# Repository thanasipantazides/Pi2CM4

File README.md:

# Pi2CM4
An adapter board for the [Raspberry Pi Compute Module 4](https://datasheets.raspberrypi.com/cm4/cm4-datasheet.pdf) that has the footprint and I/O connectors of a Raspberry Pi 2/3/[4](https://datasheets.raspberrypi.com/rpi4/raspberry-pi-4-product-brief.pdf).

## WARNING: HAS NOT BEEN TESTED.
I will update when testing is done.

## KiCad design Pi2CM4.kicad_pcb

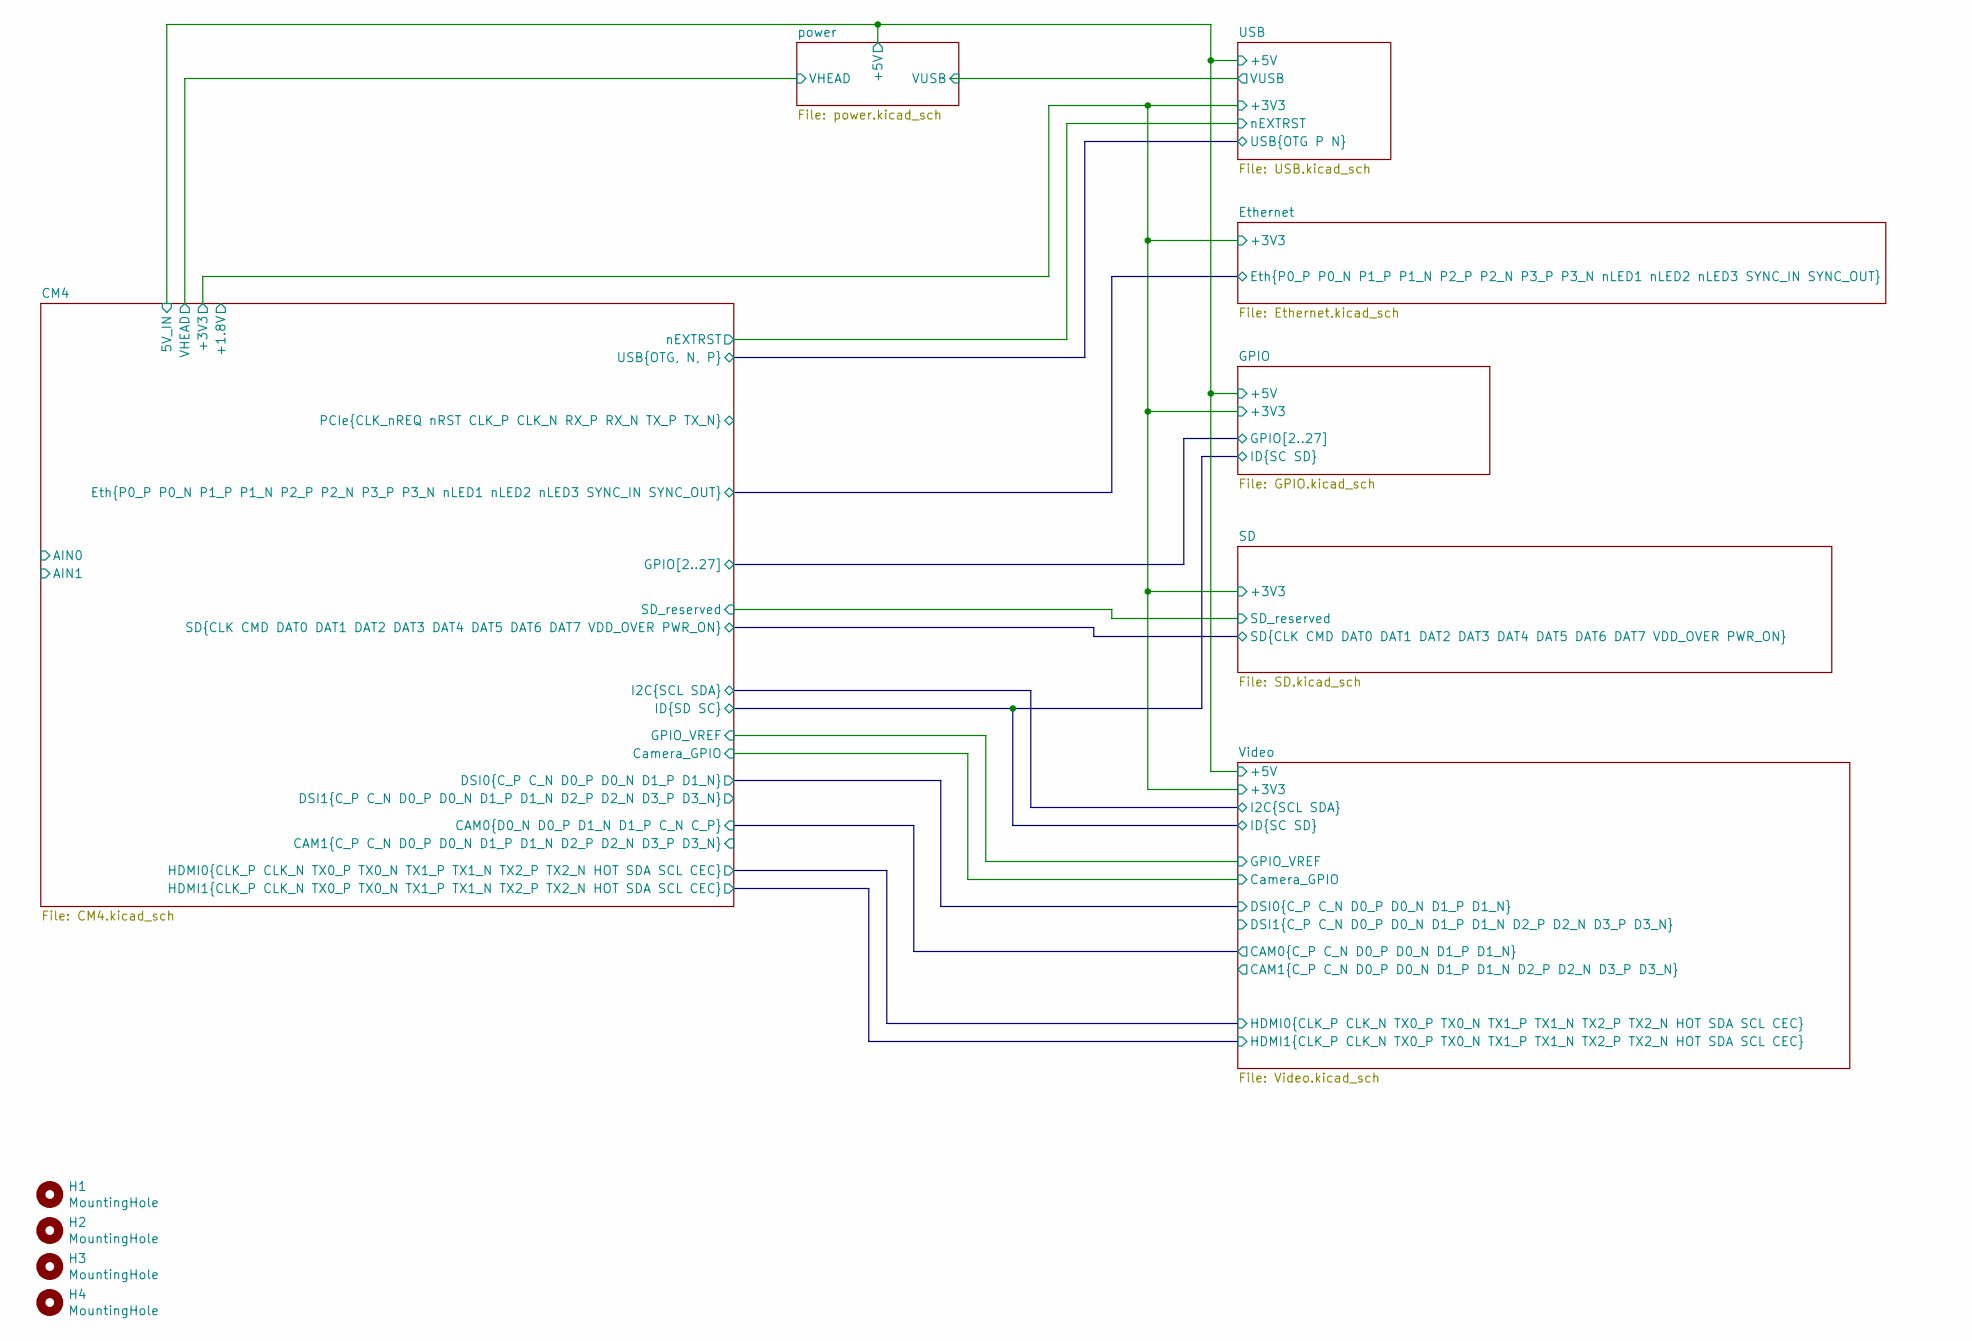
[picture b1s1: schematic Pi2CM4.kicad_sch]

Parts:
H1, H2, H3, H4: MountingHole; MountingHole_2.7mm_M2.5; Part Description M2.5 mounting hole

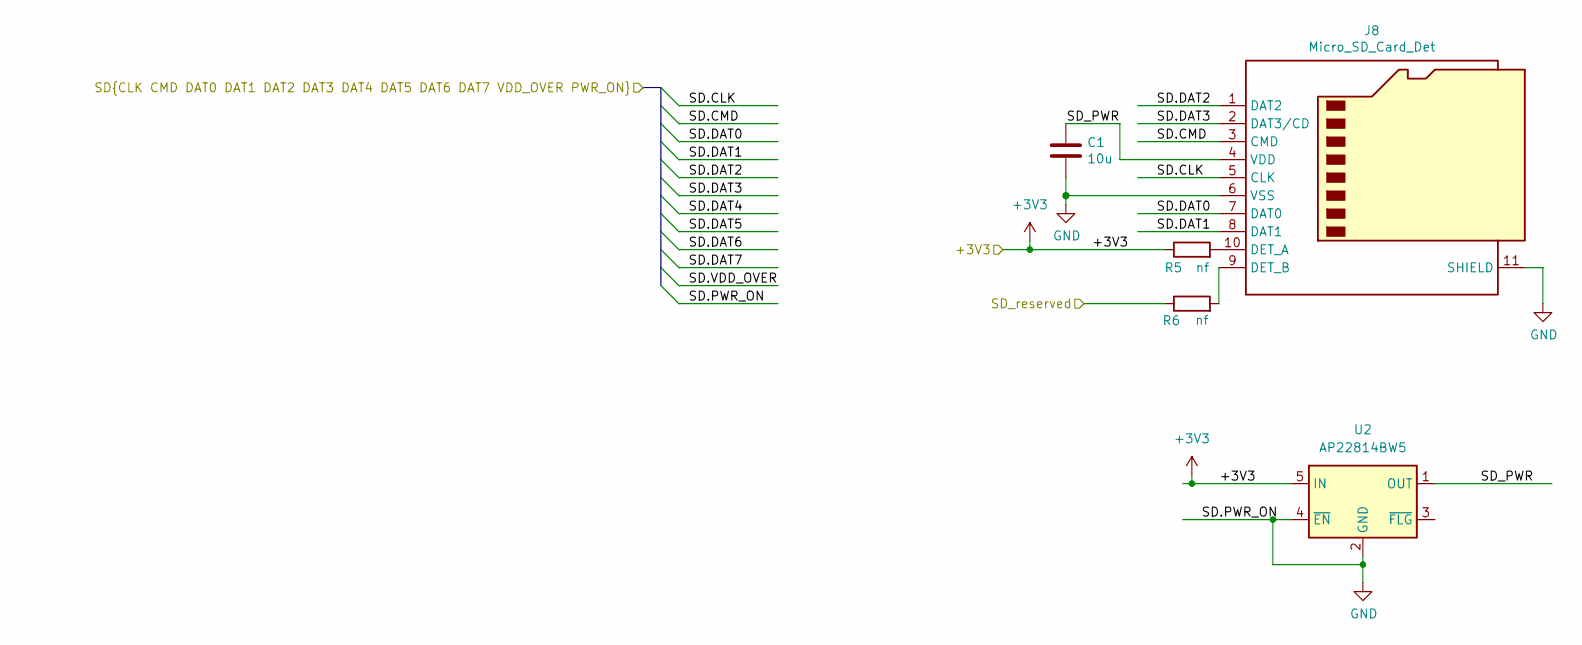
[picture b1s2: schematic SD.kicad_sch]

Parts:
C1: 10u; C_0805_2012Metric; Part Description 10uF 10% 10V Ceramic Capacitor X7R 0805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
J8: Micro_SD_Card_Det; SDCARD_MOLEX_503398-1892; Part Description 9 (8 + 1) Position Card Connector micro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
R5, R6: nf; R_0402_1005Metric; Part Description Resistor 1K M1005 1% 63mW
U2: AP22814BW5; SOT-23-5

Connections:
+3V3: R5.1, U2.5 (IN); also elsewhere on the board
/CM4/SD.CLK: J8.5 (CLK); also elsewhere on the board
/CM4/SD.CMD: J8.3 (CMD); also elsewhere on the board
/CM4/SD.DAT0: J8.7 (DAT0); also elsewhere on the board
/CM4/SD.DAT1: J8.8 (DAT1); also elsewhere on the board
/CM4/SD.DAT2: J8.1 (DAT2); also elsewhere on the board
/CM4/SD.DAT3: J8.2 (DAT3/CD); also elsewhere on the board
/CM4/SD_reserved: R6.1; also elsewhere on the board
/SD/SD_PWR: C1.1, J8.4 (VDD), U2.1 (OUT)
GND: C1.2, J8.6 (VSS), J8.11 (SHIELD), U2.2 (GND), U2.4 (~EN); also elsewhere on the board
unnamed: J8.9 (DET_B), R6.2
unnamed: J8.10 (DET_A), R5.2

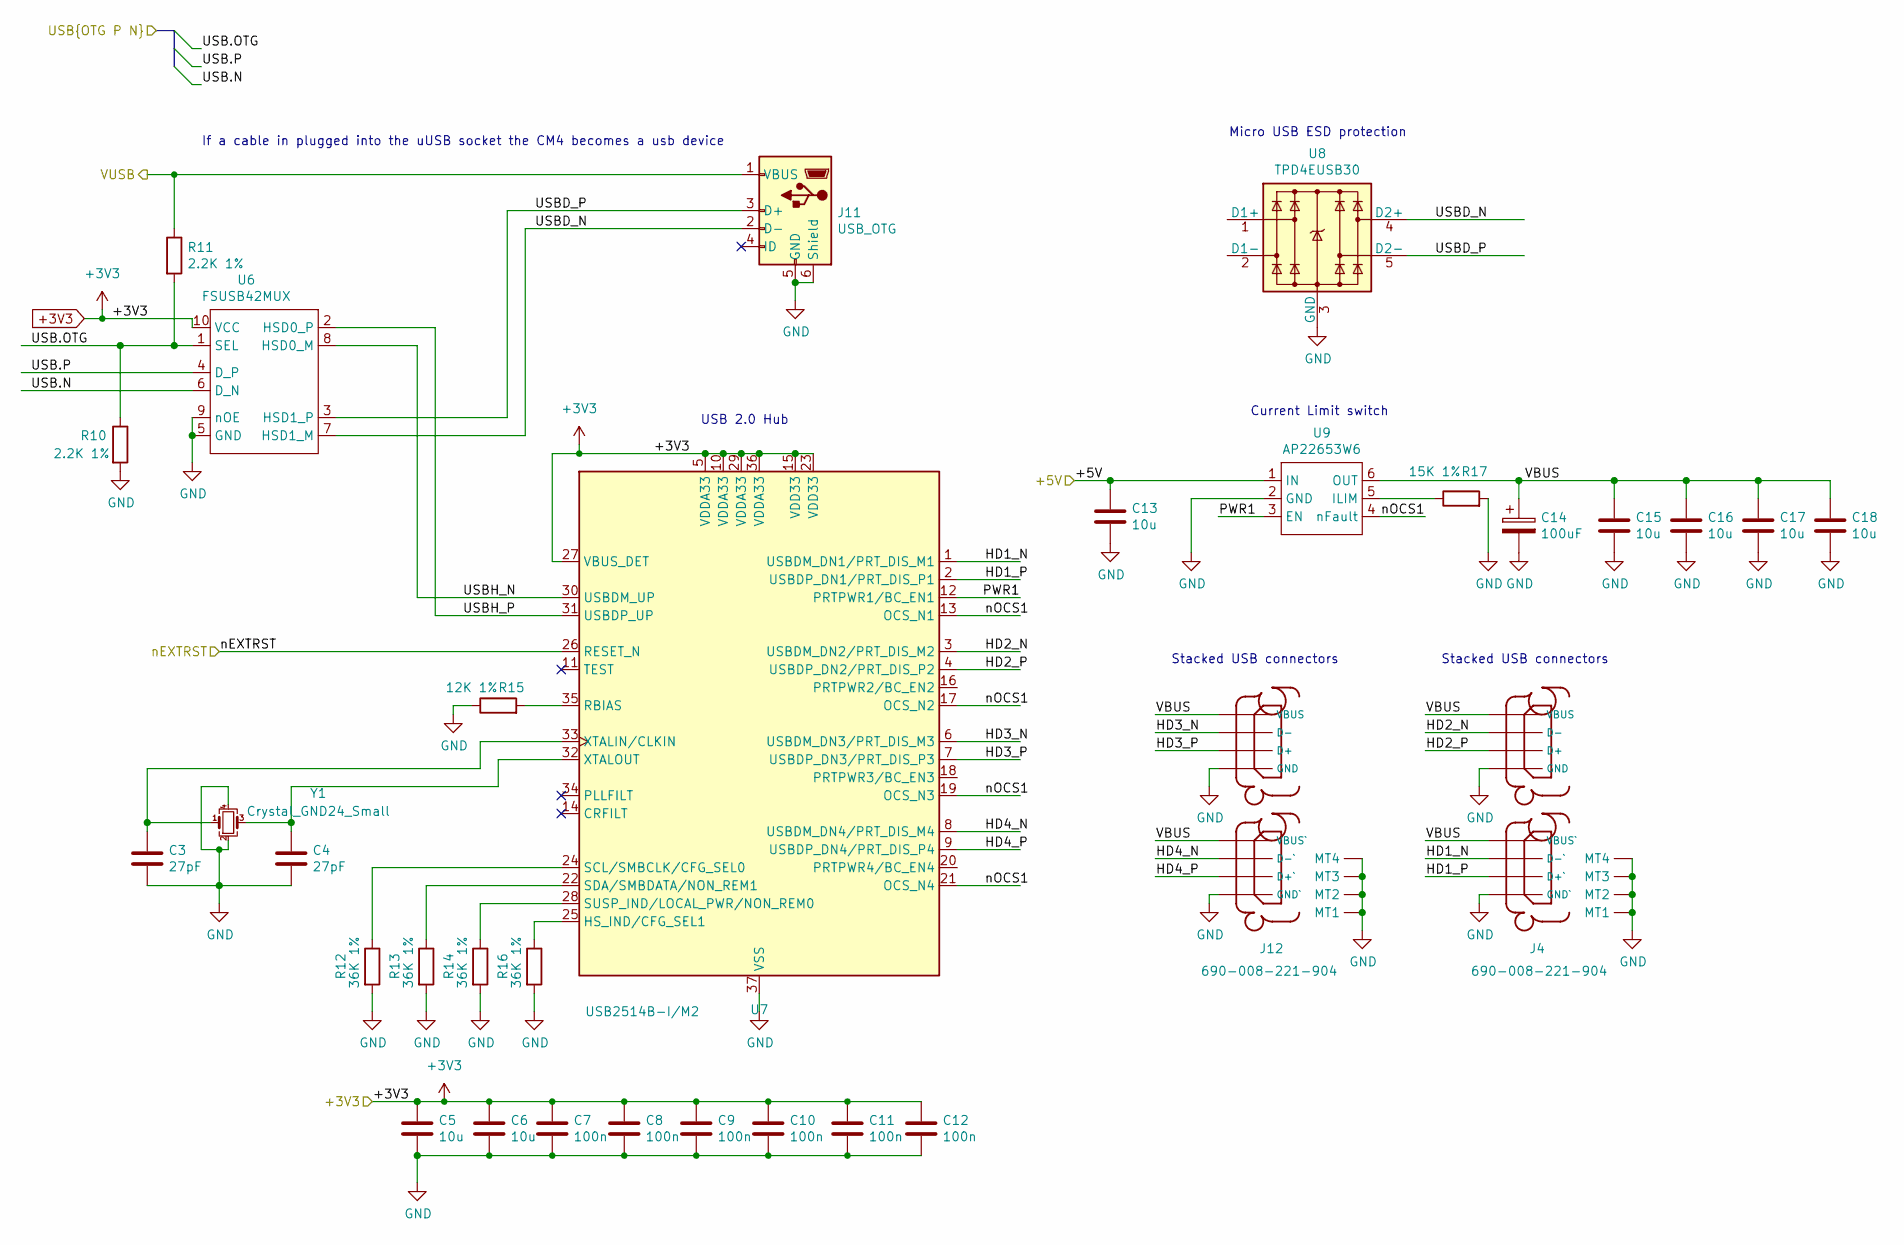
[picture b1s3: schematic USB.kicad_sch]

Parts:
C3, C4: 27pF; C_0402_1005Metric; Part Description 27pF 5% 50V Ceramic Capacitor C0G, NP0 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
C5, C6, C13, C15, C16, C17, C18: 10u; C_0805_2012Metric; Part Description 10uF 10% 10V Ceramic Capacitor X7R 0805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
C7, C8, C9, C10, C11, C12: 100n; C_0402_1005Metric; Part Description 0.1uF 10% 16V Ceramic Capacitor X7R 040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
C14: 100uF; C_1210_3225Metric; Part Description Capacitor, SP-Cap, 100u, 6.3V, 15mR ESR
J4, J12: 690-008-221-904; MOLEX_USB_67298-4090; Part Description USB-A (USB TYPE-A), Stacked Receptacle 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
J11: USB_OTG; USB_Micro-B_EDAC_UCON00686; Part Description USB - micro B USB 2.0 Receptacle Connec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
R10, R11: 2.2K 1%; R_0402_1005Metric; Part Description Resistor 2.2K M1005 1% 63mW
R12, R13, R14, R16: 36K 1%; R_0402_1005Metric; Part Description Resistor 36K M1005 1% 63mW
R15: 12K 1%; R_0402_1005Metric; Part Description Resistor 12K M1005 1% 63mW
R17: 15K 1%; R_0402_1005Metric; Part Description Resistor 15K M1005 1% 63mW
U6: FSUSB42MUX; Texas_R-PUQFN-N10; Part Description USB Switch IC 1 Channel 10-MSOP
U7: USB2514B-I/M2; QFN-36-1EP_6x6mm_P0.5mm_EP3.7x3.7mm; Part Description USB Hub Controller USB Interface 36-SQF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
U8: TPD4EUSB30; USON-10_2.5x1.0mm_P0.5mm; Part Description Quad TVS diode for high speed signals (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
U9: AP22653W6; SOT-23-6; Part Description Power Switch/Driver 1:1 P-Channel 2.1A 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
Y1: Crystal_GND24_Small; Crystal_SMD_2520-4Pin_2.5x2.0mm

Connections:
+3V3: C5.1, C6.1, C7.1, C8.1, C9.1, C10.1, C11.1, C12.1, U6.10 (VCC), U7.5 (VDDA33), U7.10 (VDDA33), U7.15 (VDD33), U7.23 (VDD33), U7.27 (VBUS_DET), U7.29 (VDDA33), U7.36 (VDDA33); also elsewhere on the board
+5V: C13.1, U9.1 (IN); also elsewhere on the board
/CM4/USB.N: U6.6 (D_N); also elsewhere on the board
/CM4/USB.OTG: R10.1, R11.2, U6.1 (SEL); also elsewhere on the board
/CM4/USB.P: U6.4 (D_P); also elsewhere on the board
/CM4/nEXTRST: U7.26 (RESET_N); also elsewhere on the board
/USB/HD1_N: J4.2 (D-`), U7.1 (USBDM_DN1/PRT_DIS_M1)
/USB/HD1_P: J4.3 (D+`), U7.2 (USBDP_DN1/PRT_DIS_P1)
/USB/HD2_N: J4.6 (D-), U7.3 (USBDM_DN2/PRT_DIS_M2)
/USB/HD2_P: J4.7 (D+), U7.4 (USBDP_DN2/PRT_DIS_P2)
/USB/HD3_N: J12.6 (D-), U7.6 (USBDM_DN3/PRT_DIS_M3)
/USB/HD3_P: J12.7 (D+), U7.7 (USBDP_DN3/PRT_DIS_P3)
/USB/HD4_N: J12.2 (D-`), U7.8 (USBDM_DN4/PRT_DIS_M4)
/USB/HD4_P: J12.3 (D+`), U7.9 (USBDP_DN4/PRT_DIS_P4)
/USB/PWR1: U7.12 (PRTPWR1/BC_EN1), U9.3 (EN)
/USB/USBD_N: J11.2 (D-), U6.7 (HSD1_M), U8.4 (D2+), U8.7
/USB/USBD_P: J11.3 (D+), U6.3 (HSD1_P), U8.5 (D2-), U8.6
/USB/USBH_N: U6.8 (HSD0_M), U7.30 (USBDM_UP)
/USB/USBH_P: U6.2 (HSD0_P), U7.31 (USBDP_UP)
/USB/VBUS: C14.1, C15.1, C16.1, C17.1, C18.1, J4.1 (VBUS`), J4.5 (VBUS), J12.1 (VBUS`), J12.5 (VBUS), U9.6 (OUT)
/USB/VUSB: J11.1 (VBUS), R11.1
/USB/nOCS1: U7.13 (OCS_N1), U7.17 (OCS_N2), U7.19 (OCS_N3), U7.21 (OCS_N4), U9.4 (nFault)
GND: C3.2, C4.2, C5.2, C6.2, C7.2, C8.2, C9.2, C10.2, C11.2, C12.2, C13.2, C14.2, C15.2, C16.2, C17.2, C18.2, J4.4 (GND`), J4.8 (GND), J4.MT1, J4.MT2, J4.MT3, J4.MT4, J11.5 (GND), J11.6 (Shield), J12.4 (GND`), J12.8 (GND), J12.MT1, J12.MT2, J12.MT3, J12.MT4, R10.2, R12.2, R13.2, R14.2, R15.1, R16.2, R17.2, U6.5 (GND), U6.9 (nOE), U7.37 (VSS), U8.3 (GND), U8.8 (GND), U9.2 (GND), Y1.2, Y1.4; also elsewhere on the board
unnamed: C3.1, U7.33 (XTALIN/CLKIN), Y1.1
unnamed: C4.1, U7.32 (XTALOUT), Y1.3
unnamed: R12.1, U7.24 (SCL/SMBCLK/CFG_SEL0)
unnamed: R13.1, U7.22 (SDA/SMBDATA/NON_REM1)
unnamed: R14.1, U7.28 (SUSP_IND/LOCAL_PWR/NON_REM0)
unnamed: R15.2, U7.35 (RBIAS)
unnamed: R16.1, U7.25 (HS_IND/CFG_SEL1)
unnamed: R17.1, U9.5 (ILIM)
unnamed: U8.1 (D1+), U8.10
unnamed: U8.2 (D1-), U8.9

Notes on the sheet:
Current Limit switch
Stacked USB connectors
Micro USB ESD protection
If a cable in plugged into the uUSB socket the CM4 becomes a usb device
USB 2.0 Hub

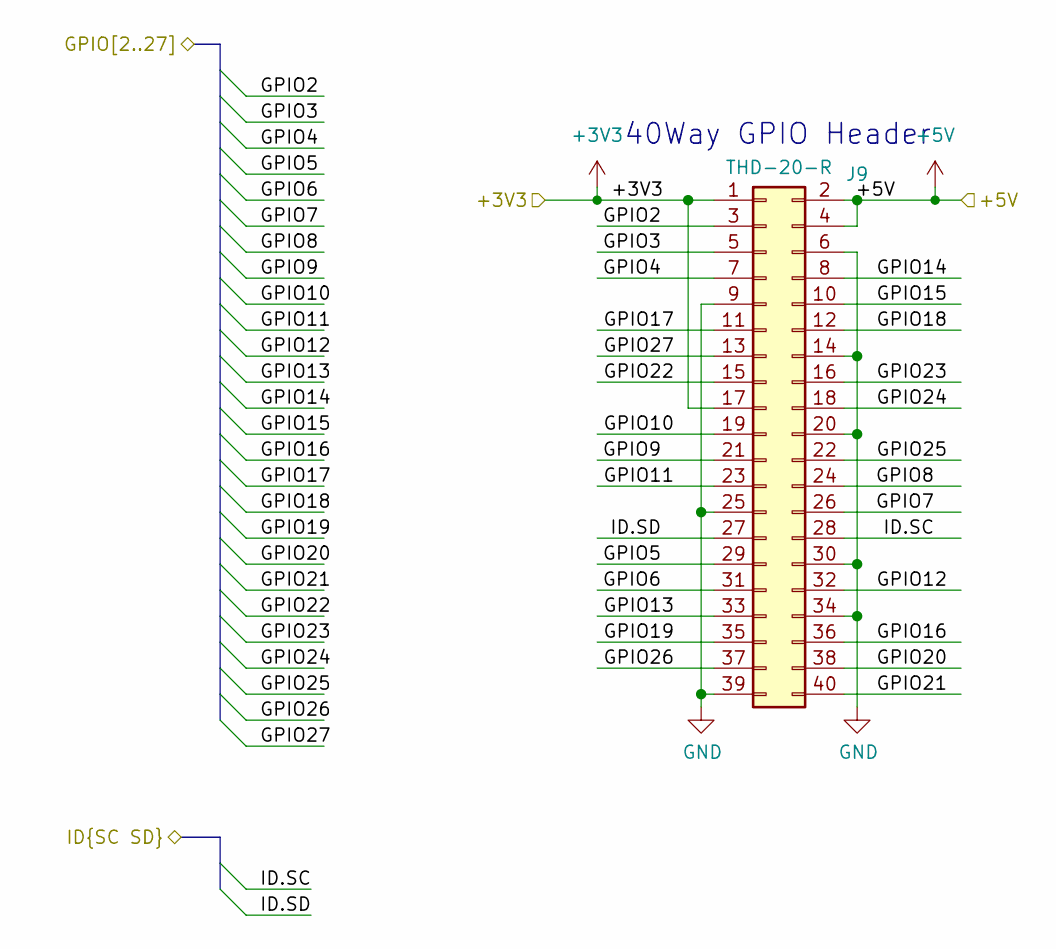
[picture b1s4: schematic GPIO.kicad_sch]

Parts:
J9: THD-20-R; PinHeader_2x20_P2.54mm_Vertical; Part Description PinHeader_2x20_P2.54mm_Vertical

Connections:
+3V3: J9.1, J9.17; also elsewhere on the board
+5V: J9.2, J9.4; also elsewhere on the board
/CM4/GPIO2: J9.3; also elsewhere on the board
/CM4/GPIO3: J9.5; also elsewhere on the board
/CM4/GPIO4: J9.7; also elsewhere on the board
/CM4/GPIO5: J9.29; also elsewhere on the board
/CM4/GPIO6: J9.31; also elsewhere on the board
/CM4/GPIO7: J9.26; also elsewhere on the board
/CM4/GPIO8: J9.24; also elsewhere on the board
/CM4/GPIO9: J9.21; also elsewhere on the board
/CM4/GPIO10: J9.19; also elsewhere on the board
/CM4/GPIO11: J9.23; also elsewhere on the board
/CM4/GPIO12: J9.32; also elsewhere on the board
/CM4/GPIO13: J9.33; also elsewhere on the board
/CM4/GPIO14: J9.8; also elsewhere on the board
/CM4/GPIO15: J9.10; also elsewhere on the board
/CM4/GPIO16: J9.36; also elsewhere on the board
/CM4/GPIO17: J9.11; also elsewhere on the board
/CM4/GPIO18: J9.12; also elsewhere on the board
/CM4/GPIO19: J9.35; also elsewhere on the board
/CM4/GPIO20: J9.38; also elsewhere on the board
/CM4/GPIO21: J9.40; also elsewhere on the board
/CM4/GPIO22: J9.15; also elsewhere on the board
/CM4/GPIO23: J9.16; also elsewhere on the board
/CM4/GPIO24: J9.18; also elsewhere on the board
/CM4/GPIO25: J9.22; also elsewhere on the board
/CM4/GPIO26: J9.37; also elsewhere on the board
/CM4/GPIO27: J9.13; also elsewhere on the board
/CM4/ID.SC: J9.28; also elsewhere on the board
/CM4/ID.SD: J9.27; also elsewhere on the board
GND: J9.6, J9.9, J9.14, J9.20, J9.25, J9.30, J9.34, J9.39; also elsewhere on the board

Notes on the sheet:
40Way GPIO Header

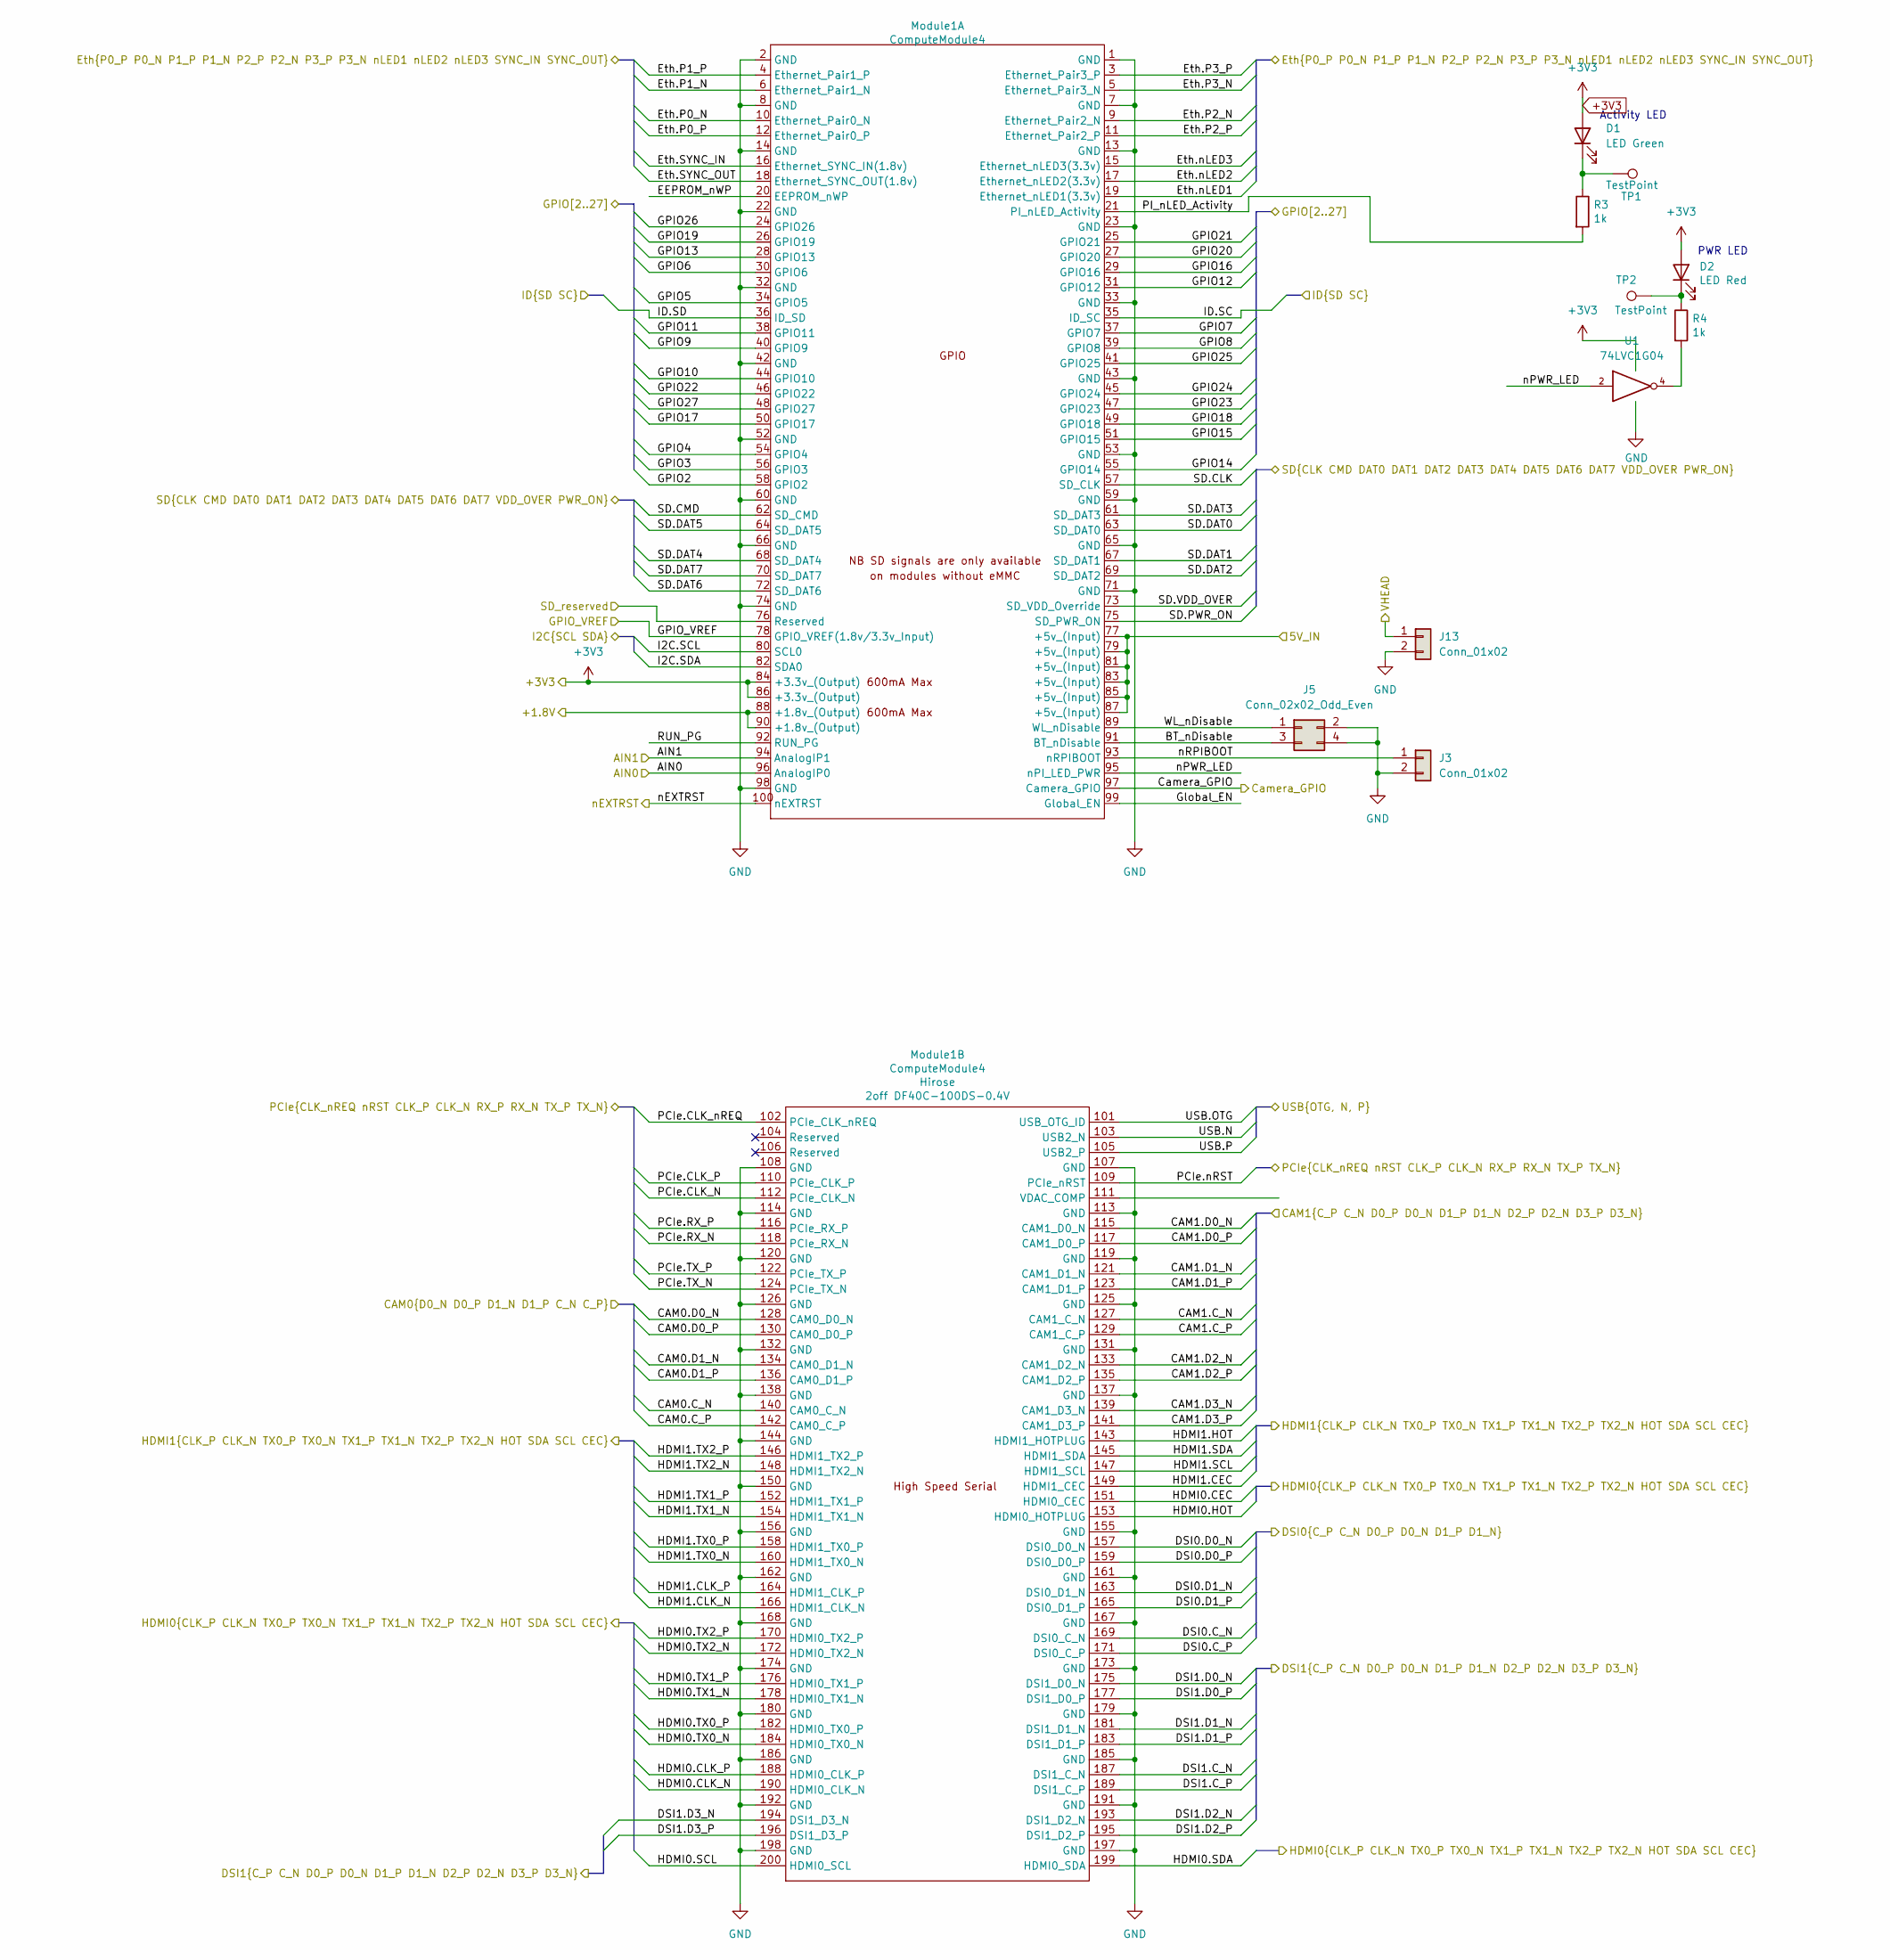
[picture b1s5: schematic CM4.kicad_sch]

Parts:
D1: LED Green; LED_0603_1608Metric; Part Description Green 572nm LED Indication - Discrete 2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
D2: LED Red; LED_0603_1608Metric; Part Description Red 620nm LED Indication - Discrete 2.2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
J3: Conn_01x02; PinHeader_1x02_P2.54mm_Vertical
J5: Conn_02x02_Odd_Even; PinSocket_2x02_P2.54mm_Vertical
J13: Conn_01x02; PinSocket_1x02_P2.54mm_Vertical
Module1: ComputeModule4; Raspberry-Pi-4-Compute-Module; Part Description 100 Position Connector Receptacle, Cent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
R3, R4: 1k; R_0402_1005Metric; Part Description Resistor 1K M1005 1% 63mW
TP1, TP2: TestPoint; TestPoint_Pad_2.0x2.0mm
U1: 74LVC1G04; SOT-23-5

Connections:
+3V3: D1.2 (A), D2.2 (A), Module1.84 (+3.3v_(Output)), Module1.86 (+3.3v_(Output)), U1.5 (VCC); also elsewhere on the board
+5V: Module1.77 (+5v_(Input)), Module1.79 (+5v_(Input)), Module1.81 (+5v_(Input)), Module1.83 (+5v_(Input)), Module1.85 (+5v_(Input)), Module1.87 (+5v_(Input)); also elsewhere on the board
/CM4/+1.8V: Module1.88 (+1.8v_(Output)), Module1.90 (+1.8v_(Output))
/CM4/AIN0: Module1.96 (AnalogIP0)
/CM4/AIN1: Module1.94 (AnalogIP1)
/CM4/BT_nDisable: J5.3, Module1.91 (BT_nDisable)
/CM4/CAM0.C_N: Module1.140 (CAM0_C_N); also elsewhere on the board
/CM4/CAM0.C_P: Module1.142 (CAM0_C_P); also elsewhere on the board
/CM4/CAM0.D0_N: Module1.128 (CAM0_D0_N); also elsewhere on the board
/CM4/CAM0.D0_P: Module1.130 (CAM0_D0_P); also elsewhere on the board
/CM4/CAM0.D1_N: Module1.134 (CAM0_D1_N); also elsewhere on the board
/CM4/CAM0.D1_P: Module1.136 (CAM0_D1_P); also elsewhere on the board
/CM4/CAM1.C_N: Module1.127 (CAM1_C_N)
/CM4/CAM1.C_P: Module1.129 (CAM1_C_P)
/CM4/CAM1.D0_N: Module1.115 (CAM1_D0_N)
/CM4/CAM1.D0_P: Module1.117 (CAM1_D0_P)
/CM4/CAM1.D1_N: Module1.121 (CAM1_D1_N)
/CM4/CAM1.D1_P: Module1.123 (CAM1_D1_P)
/CM4/CAM1.D2_N: Module1.133 (CAM1_D2_N)
/CM4/CAM1.D2_P: Module1.135 (CAM1_D2_P)
/CM4/CAM1.D3_N: Module1.139 (CAM1_D3_N)
/CM4/CAM1.D3_P: Module1.141 (CAM1_D3_P)
/CM4/Camera_GPIO: Module1.97 (Camera_GPIO); also elsewhere on the board
/CM4/DSI0.C_N: Module1.169 (DSI0_C_N); also elsewhere on the board
/CM4/DSI0.C_P: Module1.171 (DSI0_C_P); also elsewhere on the board
/CM4/DSI0.D0_N: Module1.157 (DSI0_D0_N); also elsewhere on the board
/CM4/DSI0.D0_P: Module1.159 (DSI0_D0_P); also elsewhere on the board
/CM4/DSI0.D1_N: Module1.163 (DSI0_D1_N); also elsewhere on the board
/CM4/DSI0.D1_P: Module1.165 (DSI0_D1_P); also elsewhere on the board
/CM4/DSI1.C_N: Module1.187 (DSI1_C_N)
/CM4/DSI1.C_P: Module1.189 (DSI1_C_P)
/CM4/DSI1.D0_N: Module1.175 (DSI1_D0_N)
/CM4/DSI1.D0_P: Module1.177 (DSI1_D0_P)
/CM4/DSI1.D1_N: Module1.181 (DSI1_D1_N)
/CM4/DSI1.D1_P: Module1.183 (DSI1_D1_P)
/CM4/DSI1.D2_N: Module1.193 (DSI1_D2_N)
/CM4/DSI1.D2_P: Module1.195 (DSI1_D2_P)
/CM4/DSI1.D3_N: Module1.194 (DSI1_D3_N)
/CM4/DSI1.D3_P: Module1.196 (DSI1_D3_P)
/CM4/EEPROM_nWP: Module1.20 (EEPROM_nWP)
/CM4/Eth.P0_N: Module1.10 (Ethernet_Pair0_N); also elsewhere on the board
/CM4/Eth.P0_P: Module1.12 (Ethernet_Pair0_P); also elsewhere on the board
/CM4/Eth.P1_N: Module1.6 (Ethernet_Pair1_N); also elsewhere on the board
/CM4/Eth.P1_P: Module1.4 (Ethernet_Pair1_P); also elsewhere on the board
/CM4/Eth.P2_N: Module1.9 (Ethernet_Pair2_N); also elsewhere on the board
/CM4/Eth.P2_P: Module1.11 (Ethernet_Pair2_P); also elsewhere on the board
/CM4/Eth.P3_N: Module1.5 (Ethernet_Pair3_N); also elsewhere on the board
/CM4/Eth.P3_P: Module1.3 (Ethernet_Pair3_P); also elsewhere on the board
/CM4/Eth.SYNC_IN: Module1.16 (Ethernet_SYNC_IN(1.8v))
/CM4/Eth.SYNC_OUT: Module1.18 (Ethernet_SYNC_OUT(1.8v))
/CM4/Eth.nLED1: Module1.19 (Ethernet_nLED1(3.3v))
/CM4/Eth.nLED2: Module1.17 (Ethernet_nLED2(3.3v)); also elsewhere on the board
/CM4/Eth.nLED3: Module1.15 (Ethernet_nLED3(3.3v)); also elsewhere on the board
/CM4/GPIO2: Module1.58 (GPIO2); also elsewhere on the board
/CM4/GPIO3: Module1.56 (GPIO3); also elsewhere on the board
/CM4/GPIO4: Module1.54 (GPIO4); also elsewhere on the board
/CM4/GPIO5: Module1.34 (GPIO5); also elsewhere on the board
/CM4/GPIO6: Module1.30 (GPIO6); also elsewhere on the board
/CM4/GPIO7: Module1.37 (GPIO7); also elsewhere on the board
/CM4/GPIO8: Module1.39 (GPIO8); also elsewhere on the board
/CM4/GPIO9: Module1.40 (GPIO9); also elsewhere on the board
/CM4/GPIO10: Module1.44 (GPIO10); also elsewhere on the board
/CM4/GPIO11: Module1.38 (GPIO11); also elsewhere on the board
/CM4/GPIO12: Module1.31 (GPIO12); also elsewhere on the board
/CM4/GPIO13: Module1.28 (GPIO13); also elsewhere on the board
/CM4/GPIO14: Module1.55 (GPIO14); also elsewhere on the board
/CM4/GPIO15: Module1.51 (GPIO15); also elsewhere on the board
/CM4/GPIO16: Module1.29 (GPIO16); also elsewhere on the board
/CM4/GPIO17: Module1.50 (GPIO17); also elsewhere on the board
/CM4/GPIO18: Module1.49 (GPIO18); also elsewhere on the board
/CM4/GPIO19: Module1.26 (GPIO19); also elsewhere on the board
/CM4/GPIO20: Module1.27 (GPIO20); also elsewhere on the board
/CM4/GPIO21: Module1.25 (GPIO21); also elsewhere on the board
/CM4/GPIO22: Module1.46 (GPIO22); also elsewhere on the board
/CM4/GPIO23: Module1.47 (GPIO23); also elsewhere on the board
/CM4/GPIO24: Module1.45 (GPIO24); also elsewhere on the board
/CM4/GPIO25: Module1.41 (GPIO25); also elsewhere on the board
/CM4/GPIO26: Module1.24 (GPIO26); also elsewhere on the board
/CM4/GPIO27: Module1.48 (GPIO27); also elsewhere on the board
/CM4/GPIO_VREF: Module1.78 (GPIO_VREF(1.8v/3.3v_Input)); also elsewhere on the board
/CM4/Global_EN: Module1.99 (Global_EN)
/CM4/HDMI0.CEC: Module1.151 (HDMI0_CEC); also elsewhere on the board
/CM4/HDMI0.CLK_N: Module1.190 (HDMI0_CLK_N); also elsewhere on the board
/CM4/HDMI0.CLK_P: Module1.188 (HDMI0_CLK_P); also elsewhere on the board
/CM4/HDMI0.HOT: Module1.153 (HDMI0_HOTPLUG); also elsewhere on the board
/CM4/HDMI0.SCL: Module1.200 (HDMI0_SCL); also elsewhere on the board
/CM4/HDMI0.SDA: Module1.199 (HDMI0_SDA); also elsewhere on the board
/CM4/HDMI0.TX0_N: Module1.184 (HDMI0_TX0_N); also elsewhere on the board
/CM4/HDMI0.TX0_P: Module1.182 (HDMI0_TX0_P); also elsewhere on the board
/CM4/HDMI0.TX1_N: Module1.178 (HDMI0_TX1_N); also elsewhere on the board
/CM4/HDMI0.TX1_P: Module1.176 (HDMI0_TX1_P); also elsewhere on the board
/CM4/HDMI0.TX2_N: Module1.172 (HDMI0_TX2_N); also elsewhere on the board
/CM4/HDMI0.TX2_P: Module1.170 (HDMI0_TX2_P); also elsewhere on the board
/CM4/HDMI1.CEC: Module1.149 (HDMI1_CEC); also elsewhere on the board
/CM4/HDMI1.CLK_N: Module1.166 (HDMI1_CLK_N); also elsewhere on the board
/CM4/HDMI1.CLK_P: Module1.164 (HDMI1_CLK_P); also elsewhere on the board
/CM4/HDMI1.HOT: Module1.143 (HDMI1_HOTPLUG); also elsewhere on the board
/CM4/HDMI1.SCL: Module1.147 (HDMI1_SCL); also elsewhere on the board
/CM4/HDMI1.SDA: Module1.145 (HDMI1_SDA); also elsewhere on the board
/CM4/HDMI1.TX0_N: Module1.160 (HDMI1_TX0_N); also elsewhere on the board
/CM4/HDMI1.TX0_P: Module1.158 (HDMI1_TX0_P); also elsewhere on the board
/CM4/HDMI1.TX1_N: Module1.154 (HDMI1_TX1_N); also elsewhere on the board
/CM4/HDMI1.TX1_P: Module1.152 (HDMI1_TX1_P); also elsewhere on the board
/CM4/HDMI1.TX2_N: Module1.148 (HDMI1_TX2_N); also elsewhere on the board
/CM4/HDMI1.TX2_P: Module1.146 (HDMI1_TX2_P); also elsewhere on the board
/CM4/I2C.SCL: Module1.80 (SCL0); also elsewhere on the board
/CM4/I2C.SDA: Module1.82 (SDA0); also elsewhere on the board
/CM4/ID.SC: Module1.35 (ID_SC); also elsewhere on the board
/CM4/ID.SD: Module1.36 (ID_SD); also elsewhere on the board
/CM4/PCIe.CLK_N: Module1.112 (PCIe_CLK_N)
/CM4/PCIe.CLK_P: Module1.110 (PCIe_CLK_P)
/CM4/PCIe.CLK_nREQ: Module1.102 (PCIe_CLK_nREQ)
/CM4/PCIe.RX_N: Module1.118 (PCIe_RX_N)
/CM4/PCIe.RX_P: Module1.116 (PCIe_RX_P)
/CM4/PCIe.TX_N: Module1.124 (PCIe_TX_N)
/CM4/PCIe.TX_P: Module1.122 (PCIe_TX_P)
/CM4/PCIe.nRST: Module1.109 (PCIe_nRST)
/CM4/PI_nLED_Activity: Module1.21 (PI_nLED_Activity), R3.2
/CM4/RUN_PG: Module1.92 (RUN_PG)
/CM4/SD.CLK: Module1.57 (SD_CLK); also elsewhere on the board
/CM4/SD.CMD: Module1.62 (SD_CMD); also elsewhere on the board
/CM4/SD.DAT0: Module1.63 (SD_DAT0); also elsewhere on the board
/CM4/SD.DAT1: Module1.67 (SD_DAT1); also elsewhere on the board
/CM4/SD.DAT2: Module1.69 (SD_DAT2); also elsewhere on the board
/CM4/SD.DAT3: Module1.61 (SD_DAT3); also elsewhere on the board
/CM4/SD.DAT4: Module1.68 (SD_DAT4)
/CM4/SD.DAT5: Module1.64 (SD_DAT5)
/CM4/SD.DAT6: Module1.72 (SD_DAT6)
/CM4/SD.DAT7: Module1.70 (SD_DAT7)
/CM4/SD.VDD_OVER: Module1.73 (SD_VDD_Override)
/CM4/SD_reserved: Module1.76 (Reserved); also elsewhere on the board
/CM4/USB.N: Module1.103 (USB2_N); also elsewhere on the board
/CM4/USB.OTG: Module1.101 (USB_OTG_ID); also elsewhere on the board
/CM4/USB.P: Module1.105 (USB2_P); also elsewhere on the board
/CM4/VHEAD: J13.1; also elsewhere on the board
/CM4/WL_nDisable: J5.1, Module1.89 (WL_nDisable)
/CM4/nEXTRST: Module1.100 (nEXTRST); also elsewhere on the board
/CM4/nPWR_LED: Module1.95 (nPI_LED_PWR), U1.2
/CM4/nRPIBOOT: J3.1, Module1.93 (nRPIBOOT)
GND: J3.2, J5.2, J5.4, J13.2, Module1.1 (GND), Module1.2 (GND), Module1.7 (GND), Module1.8 (GND), Module1.13 (GND), Module1.14 (GND), Module1.22 (GND), Module1.23 (GND), Module1.32 (GND), Module1.33 (GND), Module1.42 (GND), Module1.43 (GND), Module1.52 (GND), Module1.53 (GND), Module1.59 (GND), Module1.60 (GND), Module1.65 (GND), Module1.66 (GND), Module1.71 (GND), Module1.74 (GND), Module1.75 (SD_PWR_ON), Module1.98 (GND), Module1.107 (GND), Module1.108 (GND), Module1.113 (GND), Module1.114 (GND), Module1.119 (GND), Module1.120 (GND), Module1.125 (GND), Module1.126 (GND), Module1.131 (GND), Module1.132 (GND), Module1.137 (GND), Module1.138 (GND), Module1.144 (GND), Module1.150 (GND), Module1.155 (GND), Module1.156 (GND), Module1.161 (GND), Module1.162 (GND), Module1.167 (GND), Module1.168 (GND), Module1.173 (GND), Module1.174 (GND), Module1.179 (GND), Module1.180 (GND), Module1.185 (GND), Module1.186 (GND), Module1.191 (GND), Module1.192 (GND), Module1.197 (GND), Module1.198 (GND), U1.3 (GND); also elsewhere on the board
unnamed: D1.1 (K), R3.1, TP1.1
unnamed: D2.1 (K), R4.1, TP2.1
unnamed: R4.2, U1.4

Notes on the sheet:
PWR LED
Activity LED
